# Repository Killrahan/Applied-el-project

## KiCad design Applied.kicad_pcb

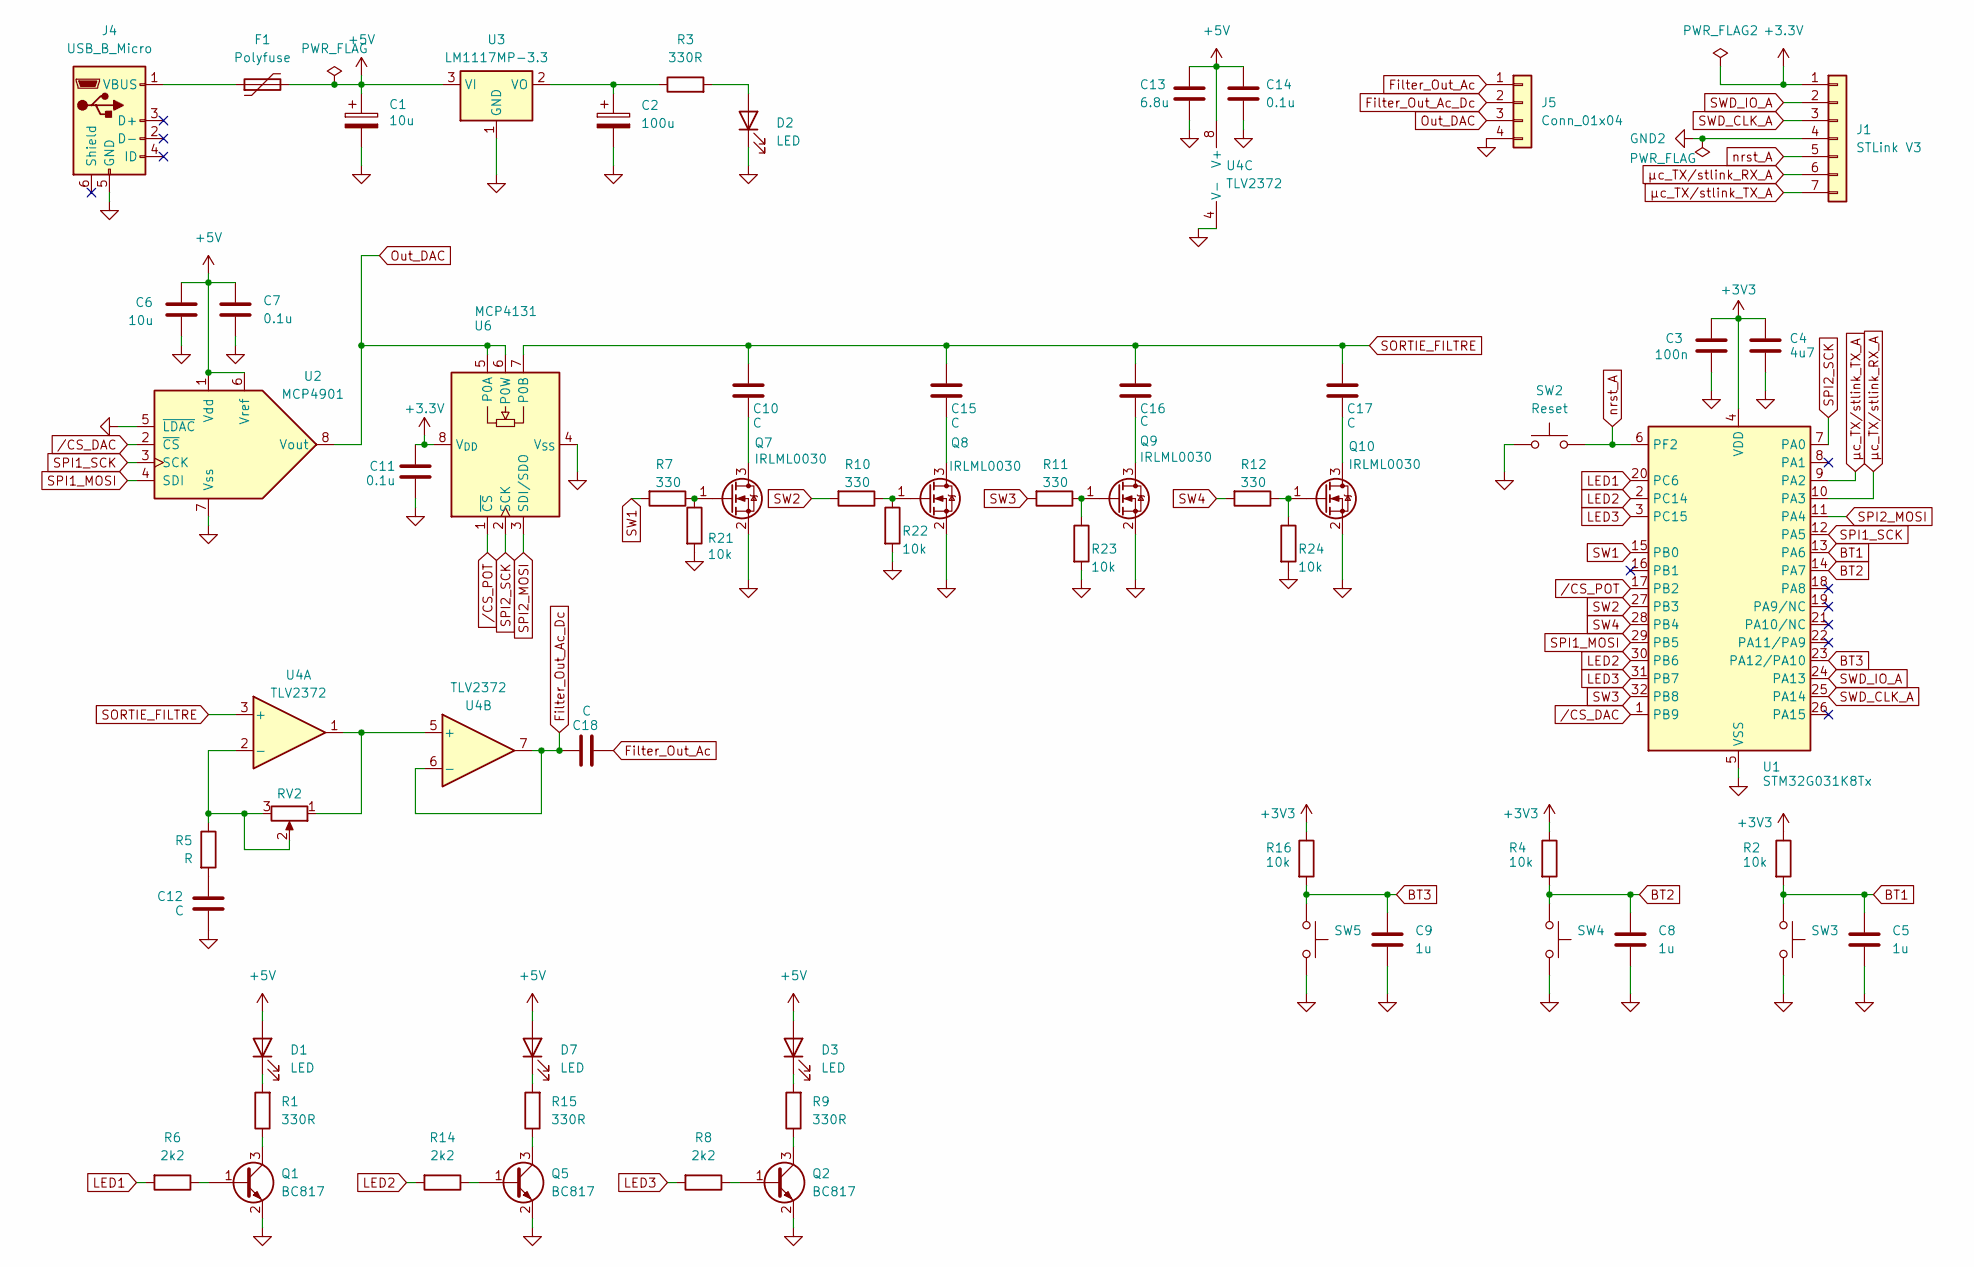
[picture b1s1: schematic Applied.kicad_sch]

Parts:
C1: 10u; C_Elec_4x5.4
C2: 100u; C_Elec_4x5.4
C3: 100n; C_0805_2012Metric_Pad1.18x1.45mm_HandSolder
C4: 4u7; C_0805_2012Metric_Pad1.18x1.45mm_HandSolder
C5, C8, C9: 1u; C_0805_2012Metric_Pad1.18x1.45mm_HandSolder
C6: 10u; C_0805_2012Metric_Pad1.18x1.45mm_HandSolder
C7, C11, C14: 0.1u; C_0805_2012Metric_Pad1.18x1.45mm_HandSolder
C10, C12, C15, C16, C17, C18: C; C_0805_2012Metric_Pad1.18x1.45mm_HandSolder
C13: 6.8u; C_0805_2012Metric_Pad1.18x1.45mm_HandSolder
D1, D2, D3, D7: LED; LED_0805_2012Metric_Pad1.15x1.40mm_HandSolder
F1: Polyfuse; Fuse_1206_3216Metric_Pad1.42x1.75mm_HandSolder
J1: STLink V3; PinHeader_1x07_P2.54mm_Vertical
J4: USB_B_Micro
J5: Conn_01x04; PinHeader_1x04_P2.54mm_Vertical
Q1, Q2, Q5: BC817; SOT-23
Q7, Q8, Q9, Q10: IRLML0030; SOT-23
R1, R3, R9, R15: 330R; R_0805_2012Metric_Pad1.20x1.40mm_HandSolder
R2, R4, R16, R21, R22, R23, R24: 10k; R_0805_2012Metric_Pad1.20x1.40mm_HandSolder
R5: R; R_0805_2012Metric_Pad1.20x1.40mm_HandSolder
R6, R8, R14: 2k2; R_0805_2012Metric_Pad1.20x1.40mm_HandSolder
R7, R10, R11, R12: 330; R_0805_2012Metric_Pad1.20x1.40mm_HandSolder
RV2: Potentiometer_Bourns_TC33X_Vertical
SW2: Reset
SW3, SW4, SW5: SW_Omron_B3FS
U1: STM32G031K8Tx; LQFP-32_7x7mm_P0.8mm
U2: MCP4901; SOIC-8_3.9x4.9mm_P1.27mm
U3: LM1117MP-3.3; SOIC-8_3.9x4.9mm_P1.27mm
U4: TLV2372; SOIC-8_3.9x4.9mm_P1.27mm
U6: MCP4131; SOIC-8_3.9x4.9mm_P1.27mm

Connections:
+3.3V: C11.2, J1.1, U6.8 (V_{DD})
+3V3: C3.1, C4.1, R2.1, R4.1, R16.1, U1.4 (VDD)
+5V: C1.1, C6.1, C7.1, C13.1, C14.1, D1.2 (A), D3.2 (A), D7.2 (A), F1.2, U2.1 (Vdd), U2.6 (Vref), U3.3 (VI), U4.8 (V+)
<NO NET>: C1.2, C2.2, C3.2, C4.2, C5.2, C6.2, C7.2, C8.2, C9.2, C11.1, C12.2, C13.2, C14.2, D2.1 (K), J4.5 (GND), J5.4, Q1.2 (E), Q2.2 (E), Q5.2 (E), Q7.2 (S), Q8.2 (S), Q9.2 (S), Q10.2 (S), R21.2, R22.2, R23.2, R24.2, SW2.1, SW3.2, SW4.2, SW5.2, U1.5 (VSS), U2.5 (~LDAC), U2.7 (Vss), U3.1 (GND), U4.4 (V-), U6.4 (V_{SS})
BT1: C5.1, R2.2, SW3.1, U1.13 (PA6)
BT2: C8.1, R4.2, SW4.1, U1.14 (PA7)
BT3: C9.1, R16.2, SW5.1, U1.23 (PA12/PA10)
Filter_Out_Ac: C18.2, J5.1
Filter_Out_Ac_Dc: C18.1, J5.2, U4.6 (-), U4.7
GND: J1.4
LED1: R6.2, U1.20 (PC6)
LED2: R14.2, U1.2 (PC14), U1.30 (PB6)
LED3: R8.2, U1.3 (PC15), U1.31 (PB7)
unnamed: C12.1, R5.2
unnamed: D1.1 (K), R1.2
unnamed: D2.2 (A), R3.2
unnamed: D3.1 (K), R9.2
unnamed: D7.1 (K), R15.2
unnamed: F1.1, J4.1 (VBUS)
unnamed: Q1.1 (B), R6.1
unnamed: Q1.3 (C), R1.1
unnamed: Q2.1 (B), R8.1
unnamed: Q2.3 (C), R9.1
unnamed: Q5.1 (B), R14.1
unnamed: Q5.3 (C), R15.1
unnamed: C10.2, Q7.3 (D)
unnamed: Q7.1 (G), R7.1, R21.1
unnamed: C15.2, Q8.3 (D)
unnamed: Q8.1 (G), R10.1, R22.1
unnamed: C16.2, Q9.3 (D)
unnamed: Q9.1 (G), R11.1, R23.1
unnamed: C17.2, Q10.3 (D)
unnamed: Q10.1 (G), R12.1, R24.1
unnamed: C2.1, R3.1, U3.2 (VO)
unnamed: R5.1, RV2.2, RV2.3, U4.2 (-)
unnamed: RV2.1, U4.1, U4.5 (+)
Out_DAC: J5.3, U2.8 (Vout), U6.5 (P0A), U6.6 (P0W)
SORTIE_FILTRE: C10.1, C15.1, C16.1, C17.1, U4.3 (+), U6.7 (P0B)
SPI1_MOSI: U1.29 (PB5), U2.4 (SDI)
SPI1_SCK: U1.12 (PA5), U2.3 (SCK)
SPI2_MOSI: U1.11 (PA4), U6.3 (SDI/SDO)
SPI2_SCK: U1.7 (PA0), U6.2 (SCK)
SW1: R7.2, U1.15 (PB0)
SW2: R10.2, U1.27 (PB3)
SW3: R11.2, U1.32 (PB8)
SW4: R12.2, U1.28 (PB4)
SWD_CLK_A: J1.3, U1.25 (PA14)
SWD_IO_A: J1.2, U1.24 (PA13)
nrst_A: J1.5, SW2.2, U1.6 (PF2)
/CS_DAC: U1.1 (PB9), U2.2 (~CS)
/CS_POT: U1.17 (PB2), U6.1 (~CS)
µc_TX/stlink_RX_A: J1.6, U1.10 (PA3)
µc_TX/stlink_TX_A: J1.7, U1.9 (PA2)

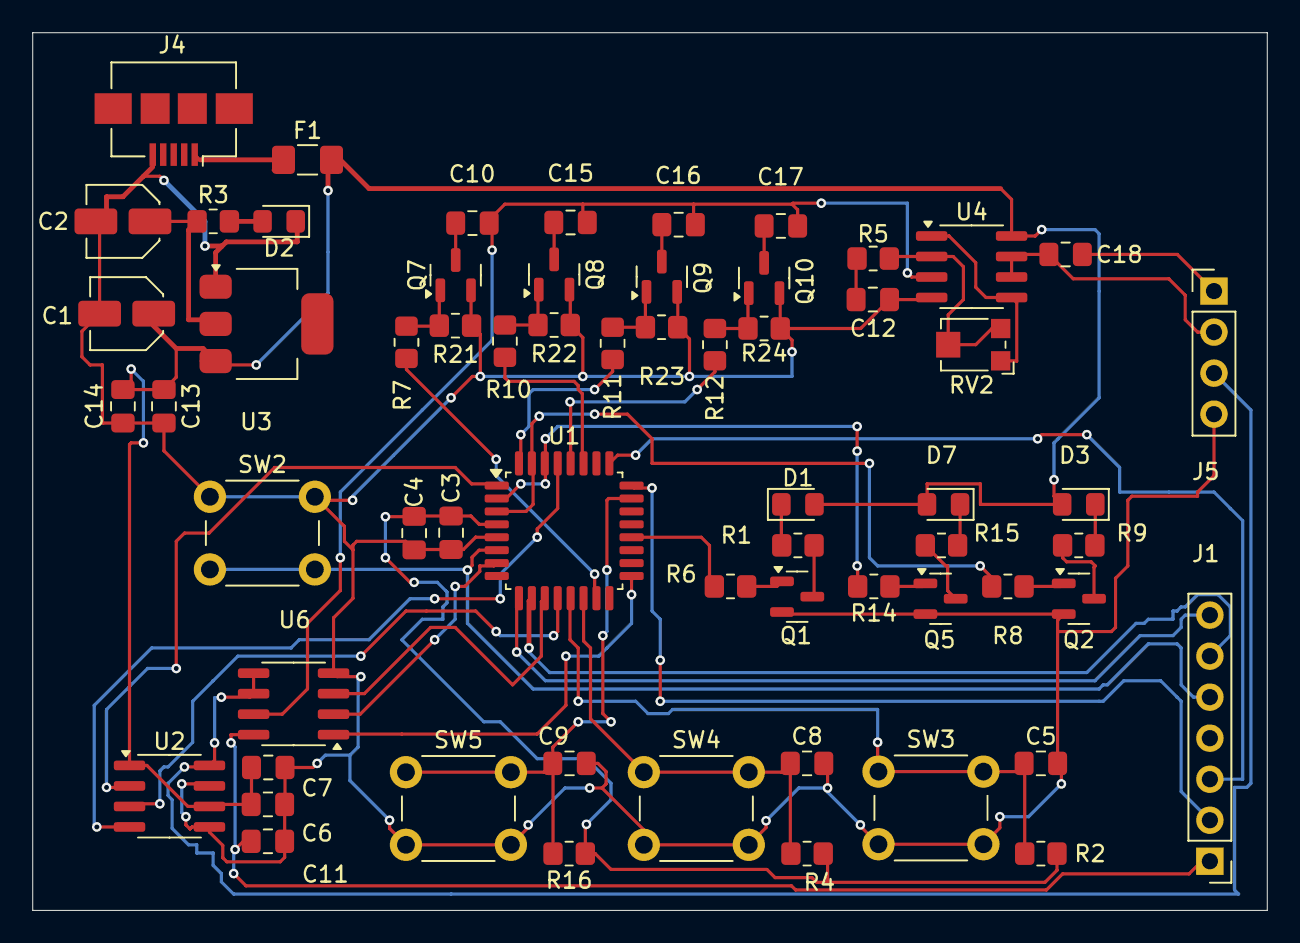
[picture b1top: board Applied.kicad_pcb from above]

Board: 2 copper layers, 76.5 x 54.4 mm, 62 parts (0 on the bottom side), 52 nets.

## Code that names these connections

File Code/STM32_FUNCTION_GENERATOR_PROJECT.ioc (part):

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Mcu.Name=STM32G031K(4-6-8)Tx
Mcu.Package=LQFP32
Mcu.UserName=STM32G031K8Tx
PA0.Mode=TX_Only_Simplex_Unidirect_Master
PA0.Signal=SPI2_SCK
PA12\ [PA10].GPIOParameters=GPIO_PuPd,GPIO_ModeDefaultEXTI
PA12\ [PA10].GPIO_ModeDefaultEXTI=GPIO_MODE_IT_FALLING
PA12\ [PA10].GPIO_PuPd=GPIO_PULLDOWN
PA12\ [PA10].Signal=GPXTI12
PA13.GPIOParameters=GPIO_Label
PA13.GPIO_Label=T_JTMS
PA13.Mode=Serial_Wire
PA13.Signal=SYS_SWDIO
PA14-BOOT0.GPIOParameters=GPIO_Label
PA14-BOOT0.GPIO_Label=T_JTCK
PA14-BOOT0.Mode=Serial_Wire
PA14-BOOT0.Signal=SYS_SWCLK
PA2.GPIOParameters=GPIO_PuPd,GPIO_Label
PA2.GPIO_Label=T_VCP_TX
PA2.GPIO_PuPd=GPIO_PULLUP
PA2.Signal=USART2_TX
PA3.GPIOParameters=GPIO_PuPd,GPIO_Label
PA3.GPIO_Label=T_VCP_RX
PA3.GPIO_PuPd=GPIO_PULLUP
PA3.Signal=USART2_RX
PA4.Mode=TX_Only_Simplex_Unidirect_Master
PA4.Signal=SPI2_MOSI
PA5.Mode=TX_Only_Simplex_Unidirect_Master
PA5.Signal=SPI1_SCK
PA6.GPIOParameters=GPIO_PuPd,GPIO_ModeDefaultEXTI
PA6.GPIO_ModeDefaultEXTI=GPIO_MODE_IT_FALLING
PA6.GPIO_PuPd=GPIO_PULLDOWN
PA6.Signal=GPXTI6
PA7.GPIOParameters=GPIO_PuPd,GPIO_ModeDefaultEXTI
PA7.GPIO_ModeDefaultEXTI=GPIO_MODE_IT_FALLING
PA7.GPIO_PuPd=GPIO_PULLDOWN
PA7.Signal=GPXTI7
PB0.GPIOParameters=GPIO_Label
PB0.GPIO_Label=SW1
PB0.Signal=GPIO_Output
PB2.Signal=GPIO_Output
PB3.GPIOParameters=GPIO_Label
PB3.GPIO_Label=SW2
PB3.Signal=GPIO_Output
PB4.GPIOParameters=GPIO_Label
PB4.GPIO_Label=SW4
PB4.Signal=GPIO_Output
PB5.Mode=TX_Only_Simplex_Unidirect_Master
PB5.Signal=SPI1_MOSI
PB8.GPIOParameters=GPIO_Label
PB8.GPIO_Label=SW3
PB8.Signal=GPIO_Output
PB9.GPIOParameters=GPIO_Label
PB9.GPIO_Label=CS
PB9.Signal=GPIO_Output
RCC.HSE_VALUE=8000000
RCC.SYSCLKFreq_VALUE=64000000
RCC.SYSCLKSource=RCC_SYSCLKSOURCE_PLLCLK
board=NUCLEO-G031K8
boardIOC=true

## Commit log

2024-10-17 Create 2
2024-10-17 Create e
2024-10-25 circuit d'alim et des datasheets
2024-10-25 code pour le dac et schéma pour amplifier le signal
2024-10-31 Add files via upload
    data sheet op amp
2024-10-31 Create uselessfile
2024-10-31 Add files via upload
    footprint TLV2372
2024-11-01 circuit
2024-11-01 datasheet
2024-11-05 schema et datasheets
2024-11-05 schéma avec filtre, ao gain et suiveur
2024-11-05 simulation du filtre
2024-11-06 Update main.c
    interrupt without callback DAC
2024-11-06 simulation ok
2024-11-06 circuit kicad
2024-11-06 Update stm32g0xx_it.c
    faster
2024-11-06 Update main.c
    faster
2024-11-06 circuit ok
2024-11-06 Create uselessfiletocreatestupidfolder
    yes
2024-11-06 Create reggregr
2024-11-08 code
2024-11-09 Schéma final
2024-11-09 Add files via upload
    final
2024-11-30 maj code
2024-11-30 fonction pour auto ajust le filtre
2024-12-10 maj 127.5/2
